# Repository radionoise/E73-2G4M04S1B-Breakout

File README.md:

# E73-2G4M04S1B nRF52832 breakout board

This is a simple breakout board for E73-2G4M04S1B Bluetooth module based on nRF52832 SoC: http://www.ebyte.com/en/product-view-news.aspx?id=243 which is intended to fit a breadboard with standard 2.54mm spacing.

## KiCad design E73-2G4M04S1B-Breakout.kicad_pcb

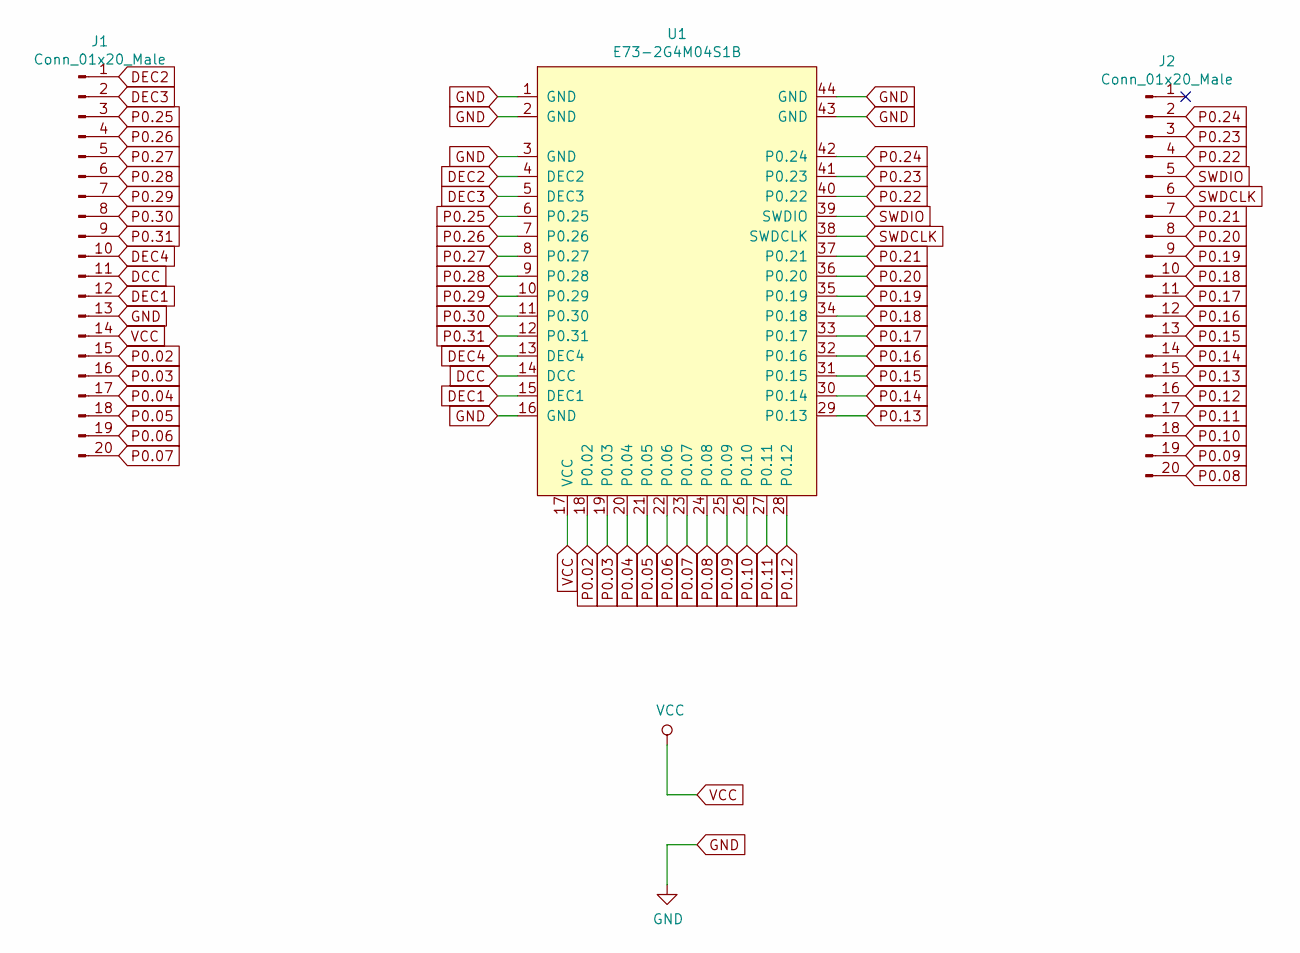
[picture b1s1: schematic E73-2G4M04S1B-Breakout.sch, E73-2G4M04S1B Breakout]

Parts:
J1, J2: Conn_01x20_Male; PinHeader_1x20_P2.54mm_Vertical
U1: E73-2G4M04S1B

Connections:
DCC: J1.11, U1.14 (DCC)
DEC1: J1.12, U1.15 (DEC1)
DEC2: J1.1, U1.4 (DEC2)
DEC3: J1.2, U1.5 (DEC3)
DEC4: J1.10, U1.13 (DEC4)
GND: J1.13, U1.1 (GND), U1.2 (GND), U1.3 (GND), U1.16 (GND), U1.43 (GND), U1.44 (GND)
P0.02: J1.15, U1.18 (P0.02)
P0.03: J1.16, U1.19 (P0.03)
P0.04: J1.17, U1.20 (P0.04)
P0.05: J1.18, U1.21 (P0.05)
P0.06: J1.19, U1.22 (P0.06)
P0.07: J1.20, U1.23 (P0.07)
P0.08: J2.20, U1.24 (P0.08)
P0.09: J2.19, U1.25 (P0.09)
P0.10: J2.18, U1.26 (P0.10)
P0.11: J2.17, U1.27 (P0.11)
P0.12: J2.16, U1.28 (P0.12)
P0.13: J2.15, U1.29 (P0.13)
P0.14: J2.14, U1.30 (P0.14)
P0.15: J2.13, U1.31 (P0.15)
P0.16: J2.12, U1.32 (P0.16)
P0.17: J2.11, U1.33 (P0.17)
P0.18: J2.10, U1.34 (P0.18)
P0.19: J2.9, U1.35 (P0.19)
P0.20: J2.8, U1.36 (P0.20)
P0.21: J2.7, U1.37 (P0.21)
P0.22: J2.4, U1.40 (P0.22)
P0.23: J2.3, U1.41 (P0.23)
P0.24: J2.2, U1.42 (P0.24)
P0.25: J1.3, U1.6 (P0.25)
P0.26: J1.4, U1.7 (P0.26)
P0.27: J1.5, U1.8 (P0.27)
P0.28: J1.6, U1.9 (P0.28)
P0.29: J1.7, U1.10 (P0.29)
P0.30: J1.8, U1.11 (P0.30)
P0.31: J1.9, U1.12 (P0.31)
SWDCLK: J2.6, U1.38 (SWDCLK)
SWDIO: J2.5, U1.39 (SWDIO)
VCC: J1.14, U1.17 (VCC)

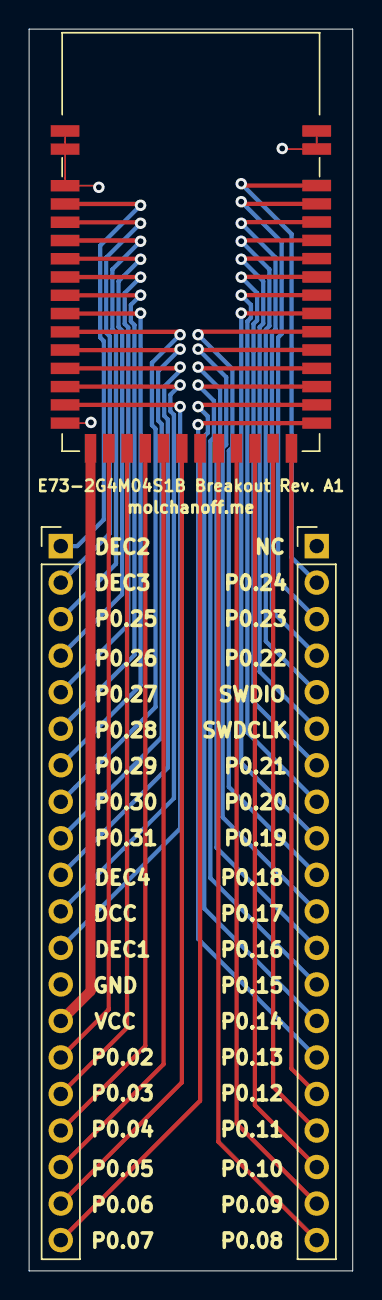
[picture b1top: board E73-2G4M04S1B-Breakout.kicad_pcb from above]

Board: 2 copper layers, 22.5 x 86.3 mm, 3 parts (0 on the bottom side), 39 nets.

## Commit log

2020-04-30 Added copper fill
2020-04-30 Added pin names
2020-04-30 Added schematic PDF and Gerber files
2020-04-30 Added board dimensions
2020-06-09 Added images
2020-06-09 Changed render file extension
2020-06-09 Added README
2020-06-09 Removed old file
2020-06-09 Added LICENSE
